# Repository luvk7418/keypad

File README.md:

This repository has the files I made in designing a two-key keypad, particularly the PCB and the case I used for it. This keypad was designed for a school project where I could make anything I wanted, or explain the physics of something.

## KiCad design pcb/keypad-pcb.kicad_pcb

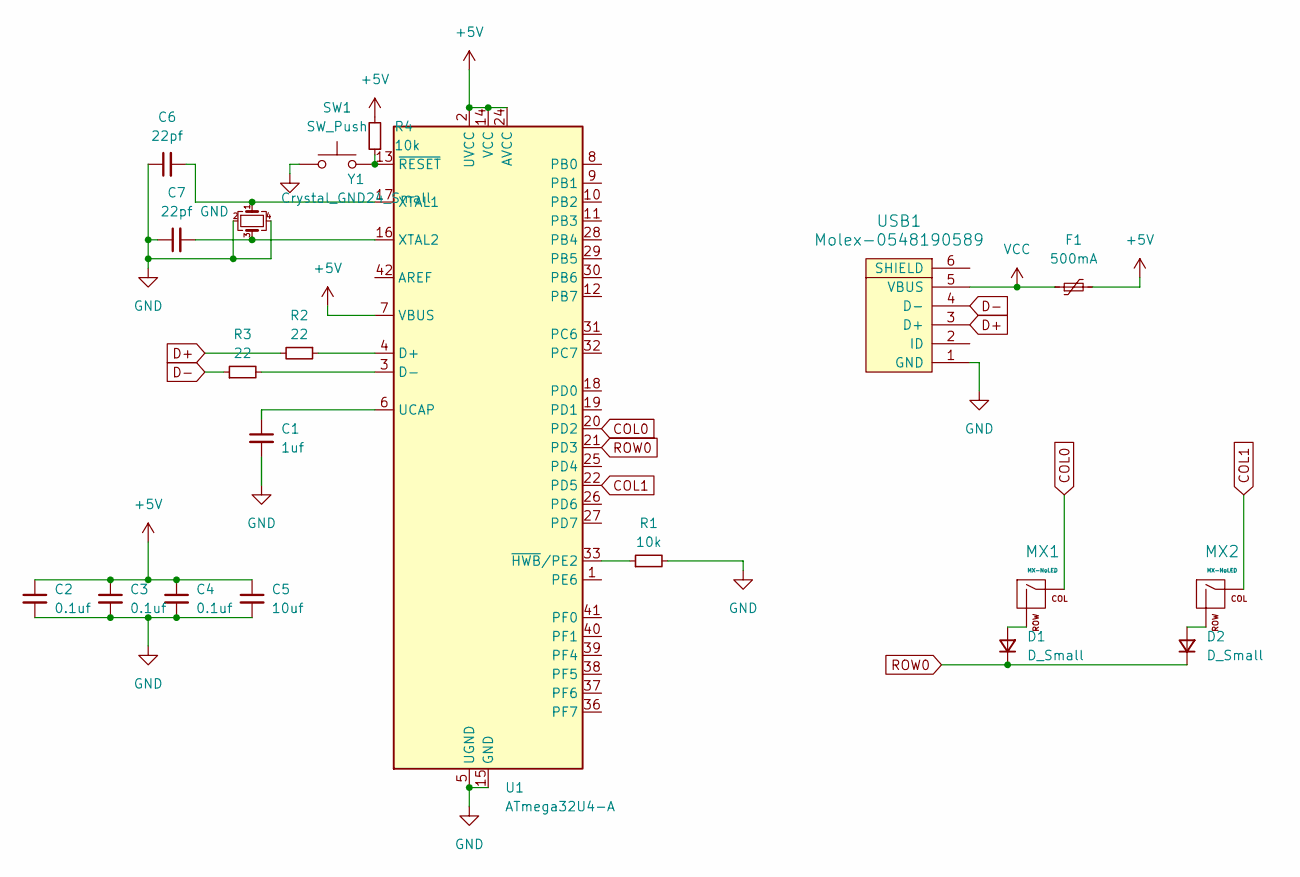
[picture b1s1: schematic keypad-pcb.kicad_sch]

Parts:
C1: 1uf; C_0805_2012Metric
C2, C3, C4: 0.1uf; C_0805_2012Metric
C5: 10uf; C_0805_2012Metric
C6, C7: 22pf; C_0805_2012Metric
D1, D2: D_Small; D_SOD-123
F1: 500mA; Fuse_1206_3216Metric
MX1, MX2: MX-NoLED; MX-1U-NoLED
R1, R4: 10k; R_0805_2012Metric
R2, R3: 22; R_0805_2012Metric
SW1: SW_Push; SKQG-1155865
U1: ATmega32U4-A; TQFP-44_10x10mm_P0.8mm
USB1: Molex-0548190589
Y1: Crystal_GND24_Small; Crystal_SMD_3225-4Pin_3.2x2.5mm

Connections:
+5V: C2.1, C3.1, C4.1, C5.1, F1.2, R4.2, U1.2 (UVCC), U1.7 (VBUS), U1.14 (VCC), U1.24 (AVCC), U1.34 (VCC), U1.44 (AVCC)
COL0: MX1.1 (COL), U1.20 (PD2)
COL1: MX2.1 (COL), U1.22 (PD5)
D+: R2.2, USB1.3 (D+)
D-: R3.1, USB1.4 (D-)
GND: C1.2, C2.2, C3.2, C4.2, C5.2, C6.1, C7.1, R1.2, SW1.1, U1.5 (UGND), U1.15 (GND), U1.23 (GND), U1.35 (GND), U1.43 (GND), USB1.1 (GND), Y1.2, Y1.4
unnamed: D1.2 (A), MX1.2 (ROW)
unnamed: D2.2 (A), MX2.2 (ROW)
unnamed: R2.1, U1.4 (D+)
unnamed: R3.2, U1.3 (D-)
unnamed: C1.1, U1.6 (UCAP)
unnamed: C6.2, U1.17 (XTAL1), Y1.1
unnamed: C7.2, U1.16 (XTAL2), Y1.3
unnamed: R1.1, U1.33 (~HWB/PE2)
unnamed: R4.1, SW1.2, U1.13 (~RESET)
ROW0: D1.1 (K), D2.1 (K), U1.21 (PD3)
VCC: F1.1, USB1.5 (VBUS)

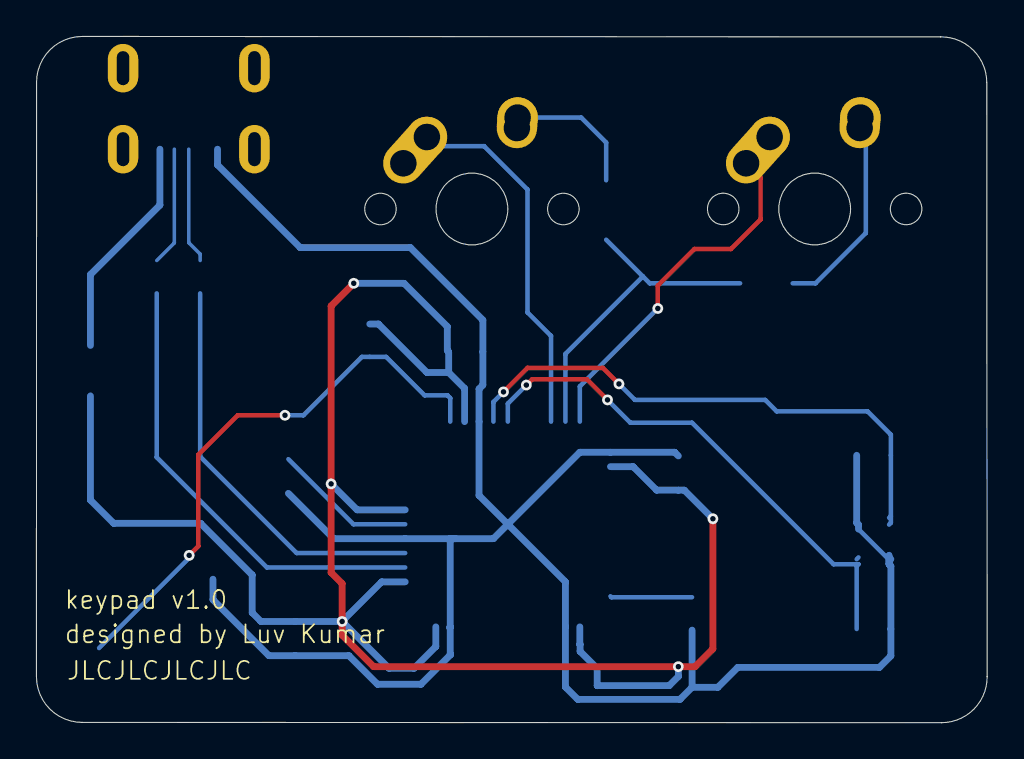
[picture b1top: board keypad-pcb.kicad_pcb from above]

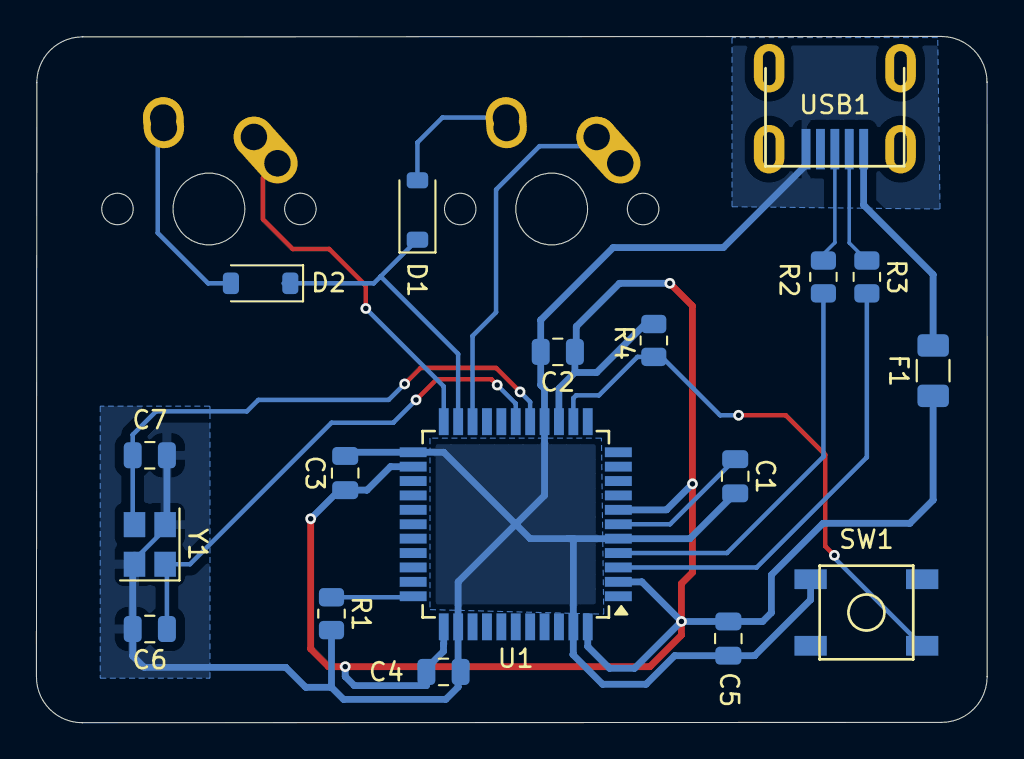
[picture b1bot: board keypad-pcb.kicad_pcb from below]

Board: 2 copper layers, 52.8 x 38.1 mm, 20 parts (18 on the bottom side), 17 nets.

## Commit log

2024-12-03 made blank pcb file
2024-12-03 add submodules
2024-12-03 add footprint libraries
2024-12-03 added mcu and usb to schematic
2024-12-03 schematic complete
2024-12-03 reorganized schematic and added footprints
2024-12-03 pcb layout done
2024-12-04 finalized pcb and created gerbers
2024-12-04 redesigned pcb for front-facing usb
2024-12-04 added silkscreened name and serial number and regenerated gerbers
2024-12-04 finalized finalized
2024-12-04 added dxf files for top and bottom case
2024-12-10 re-made manufacture files
2024-12-10 fixed bom
